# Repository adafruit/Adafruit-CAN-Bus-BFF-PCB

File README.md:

## Adafruit CAN Bus BFF Add-On for QT Py PCB

<a href="http://www.adafruit.com/products/5877"><br/>
Click here to purchase one from the Adafruit shop</a>

PCB files for the Adafruit CAN Bus BFF Add-On for QT Py. 

Format is EagleCAD schematic and board layout
* https://www.adafruit.com/product/5877

### Description

Our QT Py boards are a great way to make very small microcontroller projects that pack a ton of power - and now we have a way for you to turn many QT Py boards into powerful CAN bus devices that are super small!

CAN Bus is a small-scale networking standard, originally designed for cars and, yes, busses, but is now used for many robotics or sensor networks that need better range and addressing than I2C, and don't have the pins or computational ability to talk on Ethernet. CAN is 2 wire differential, which means it's good for long distances and noisy environments.

Messages are sent at about 1Mbps rate - you set the frequency for the bus and then all 'joiners' must match it, and have an address before the packet so that each node can listen in to messages just for it. New nodes can be attached easily because they just need to connect to the two data lines anywhere in the shared net. Each CAN devices sends messages whenever it wants, and thanks to some clever data encoding, can detect if there's a message collision and retransmit later. 

If you'd like to connect your QT Py or Xiao to a CAN Bus, the Adafruit CAN Bus BFF will work with any and all boards thanks to the simple SPI interface! The controller used is the MCP26525 - also known as the MCP2515 controller plus MCP2551 transceiver, an extremely popular and well-supported chipset that has drivers in Arduino and CircuitPython and only requires an SPI port and 1 pin for chip-select, plus another for optional IRQ. Use it to send and receive messages in either standard or extended format at up to 1 Mbps.

We've added a few nice extras to this BFF to make it useful in many common CAN scenarios:

* JST PH socket - Plug in one of our JST PH 3-pn cables (not included!) for fast wiring and connection/disconnection. Black wire is ground, Red wire is CAN H, White wire is CAN L.
* 120 ohm termination resistor on board, you can remove the termination easily by cutting the jumper on the top of the board.
* Pre-connected CS pin to A3. There's also jumpers if you want to connect the IRQ, Reset and Silent pins.

We include some header that you can solder to your QT Py. You can also pick up an Itsy Bitsy short female header kit to make it removable but compact, you'll just need to trim down the headers to 7 pins long. Works with any QT Py or Xiao-shaped board that has the SPI port and A3 pin available.

QT Py and JST PH 3-Pin cable is not included.

### License

Adafruit invests time and resources providing this open source design, please support Adafruit and open-source hardware by purchasing products from [Adafruit](https://www.adafruit.com)!

Designed by Limor Fried/Ladyada for Adafruit Industries.

Creative Commons Attribution/Share-Alike, all text above must be included in any redistribution. 
See license.txt for additional details.

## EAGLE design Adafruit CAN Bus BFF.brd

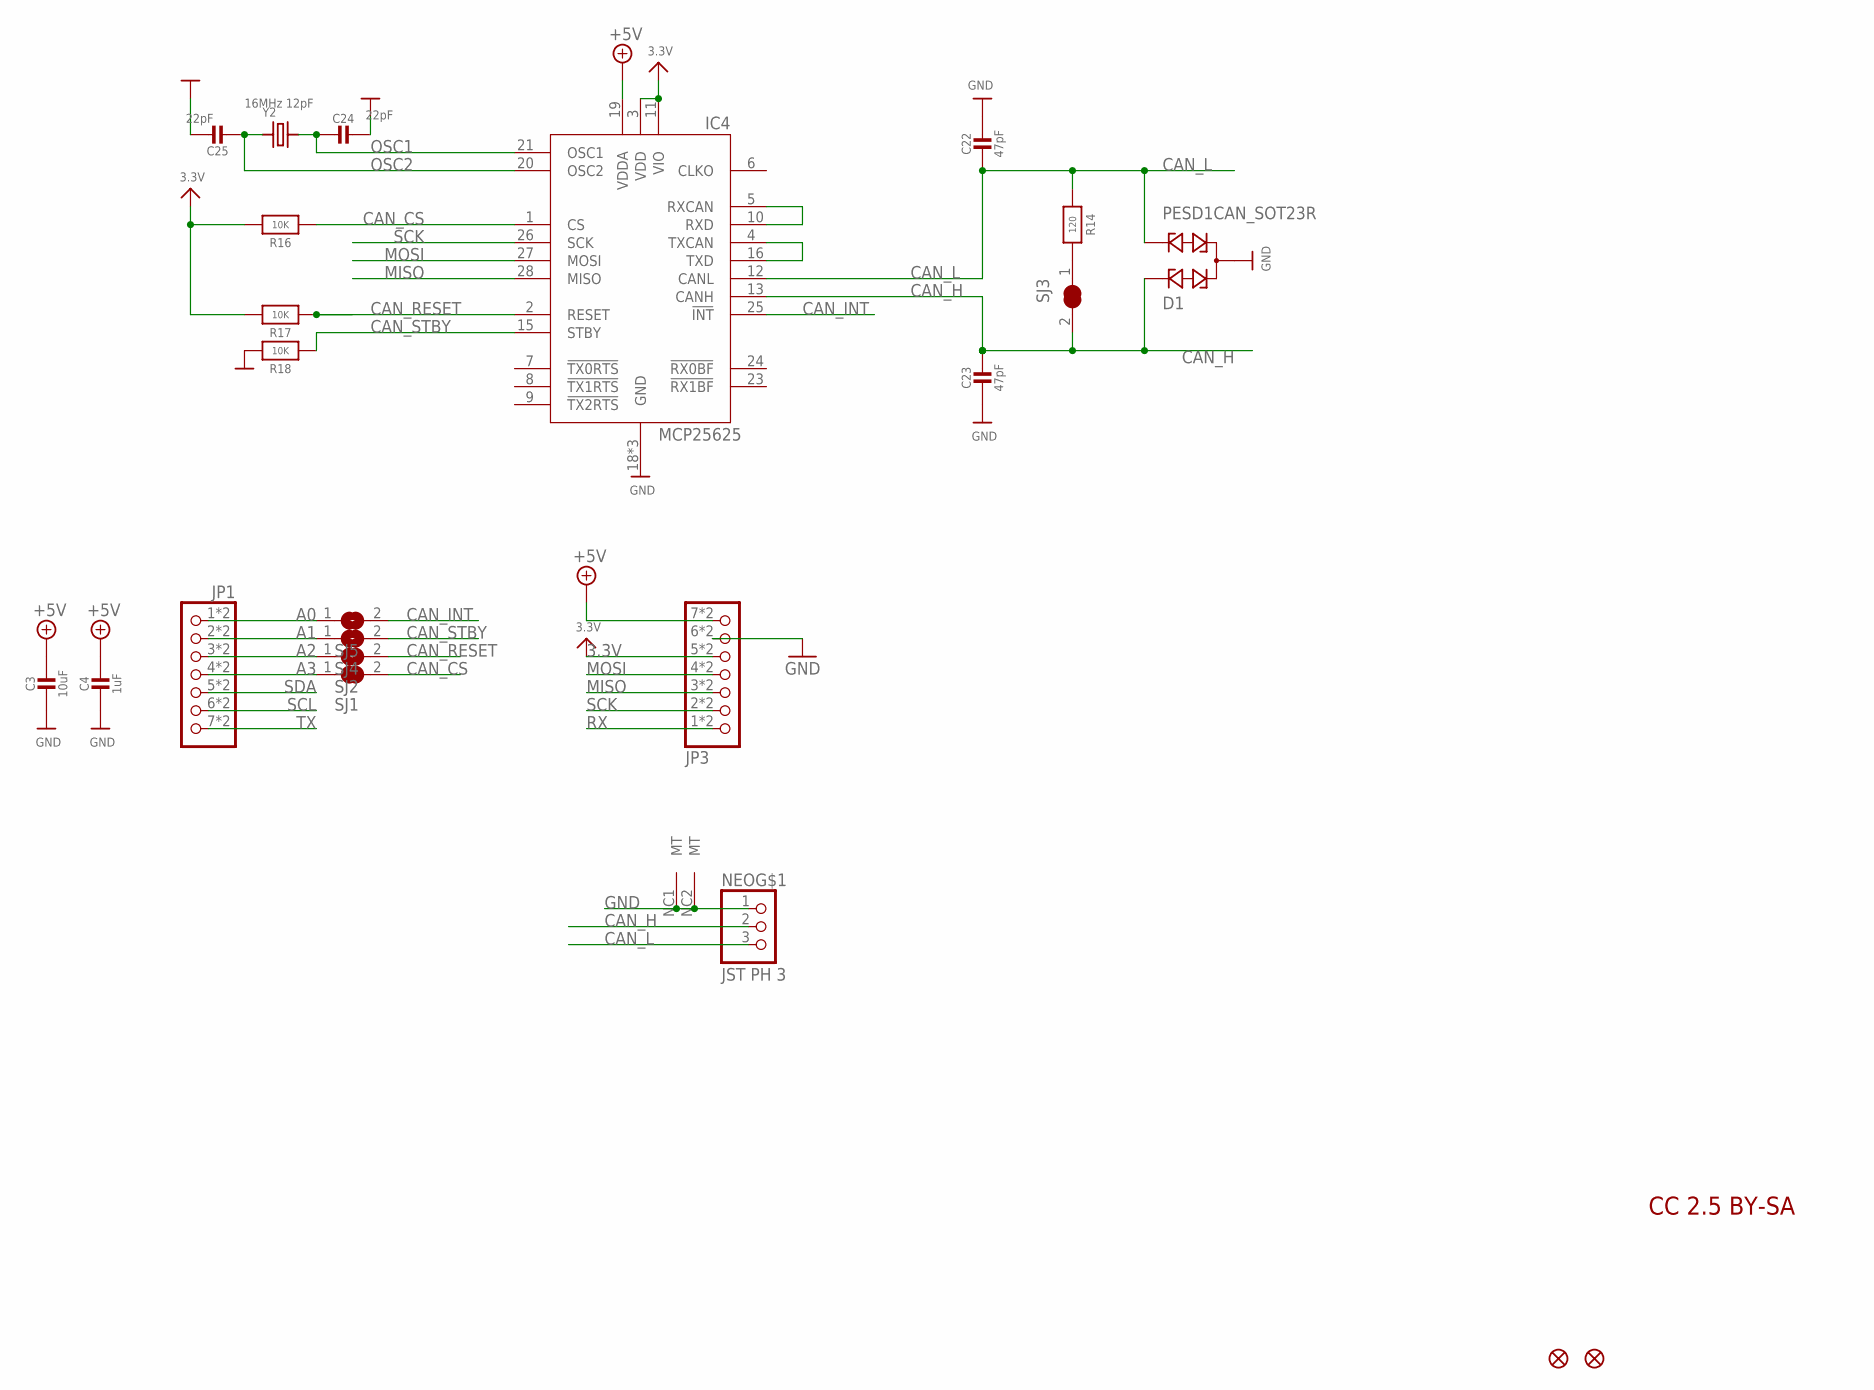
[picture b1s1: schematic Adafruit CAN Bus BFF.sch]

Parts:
C3: 10uF; 0805-NO
C4: 1uF; 0603-NO
C22, C23: 47pF; _0402NO
C24, C25: 22pF; _0402NO
D1: PESD1CAN_SOT23R; SOT23-R
IC4: MCP25625; QFN28-ML_6X6MM
JP1, JP3: HEADER-1X7_CASTEL; 1X07_CASTEL
NEO: JST PH 3; JSTPH3
R14: 120; _0402NO
R16, R17, R18: 10K; _0402NO
SJ1, SJ3: SOLDERJUMPER_CLOSED; SOLDERJUMPER_CLOSEDWIRE
SJ2, SJ4, SJ5: SOLDERJUMPER; SOLDERJUMPER_ARROW_NOPASTE
U$6, U$8: FIDUCIAL_1MM
Y2: 16MHz 12pF; CRYSTAL_2.5X2

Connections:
3.3V: IC4.3 (VDD), IC4.11 (VIO), JP3.5, JP3.5C (5), R16.2, R17.2
+5V: C3.1, C4.1, IC4.19 (VDDA), JP3.7, JP3.7C (7)
A0: JP1.1, JP1.1C (1), SJ5.1
A1: JP1.2, JP1.2C (2), SJ4.1
A2: JP1.3, JP1.3C (3), SJ2.1
A3: JP1.4, JP1.4C (4), SJ1.1
CAN_CS: IC4.1 (CS), R16.1, SJ1.2
CAN_H: C23.1, D1.1, IC4.13 (CANH), NEO.2, SJ3.2
CAN_INT: IC4.25 (!INT), SJ5.2
CAN_L: C22.2, D1.2, IC4.12 (CANL), NEO.3, R14.1
CAN_RESET: IC4.2 (RESET), R17.1, SJ2.2
CAN_STBY: IC4.15 (STBY), R18.1, SJ4.2
GND: C3.2, C4.2, C22.1, C23.2, C24.1, C25.1, D1.3, IC4.18 (GND), IC4.22 (GND), IC4.EXP (GND), JP3.6, JP3.6C (6), NEO.1, NEO.NC1 (MT), NEO.NC2 (MT), R18.2
MISO: IC4.28 (MISO), JP3.3, JP3.3C (3)
MOSI: IC4.27 (MOSI), JP3.4, JP3.4C (4)
unnamed: R14.2, SJ3.1
unnamed: IC4.5 (RXCAN), IC4.10 (RXD)
unnamed: IC4.4 (TXCAN), IC4.16 (TXD)
OSC1: C24.2, IC4.21 (OSC1), Y2.3 (2)
OSC2: C25.2, IC4.20 (OSC2), Y2.1
RX: JP3.1, JP3.1C (1)
SCK: IC4.26 (SCK), JP3.2, JP3.2C (2)
SCL: JP1.6, JP1.6C (6)
SDA: JP1.5, JP1.5C (5)
TX: JP1.7, JP1.7C (7)

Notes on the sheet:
CC 2.5 BY-SA

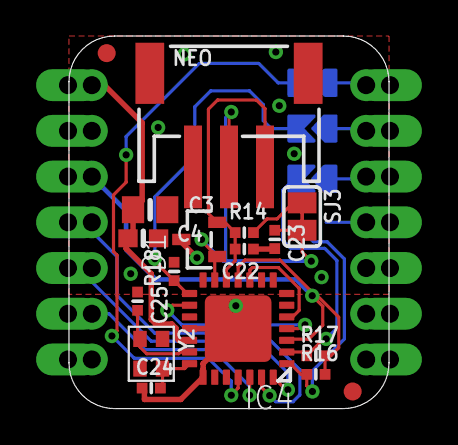
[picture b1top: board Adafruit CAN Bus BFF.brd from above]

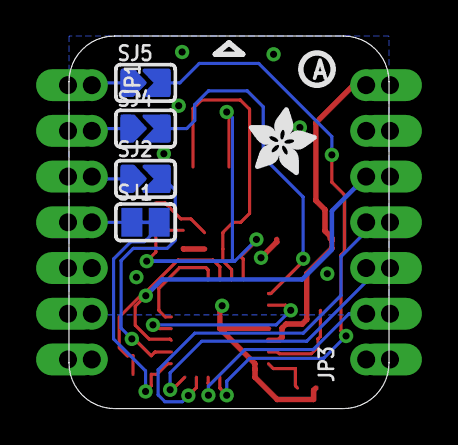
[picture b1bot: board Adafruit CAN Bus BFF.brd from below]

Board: 2 copper layers, 17.8 x 20.7 mm, 49 parts (15 on the bottom side), 25 nets.

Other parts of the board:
PLABEL1: PLABEL1
PLABEL2: PLABEL2
PLABEL3: PLABEL3
PLABEL4: PLABEL4
PLABEL5: PLABEL5
PLABEL6: PLABEL6
PLABEL7: PLABEL7
PLABEL8: PLABEL8
PLABEL9: PLABEL9
PLABEL11: PLABEL11
PLABEL12: PLABEL12
PLABEL13: PLABEL13
PLABEL14: PLABEL14
PLABEL19: PLABEL19
PLABEL20: PLABEL20
PLABEL21: PLABEL21
PLABEL22: PLABEL22
PLABEL23: PLABEL23
PLABEL24: PLABEL24
PLABEL25: PLABEL25
PLABEL26: PLABEL26
PLABEL27: PLABEL27
PLABEL28: PLABEL28
PLABEL29: PLABEL29
U$3: PCBFEAT-REV-040
U$5: ADAFRUIT_3.5MM

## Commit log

2024-01-26 cookiecutter output

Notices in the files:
parts and their libraries:
microbuilder: This work is placed in the public domain, and may be freely used for commercial and non-commercial work with the following conditions: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
